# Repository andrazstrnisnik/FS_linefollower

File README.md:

# FS_linefollower
Line follower robot project

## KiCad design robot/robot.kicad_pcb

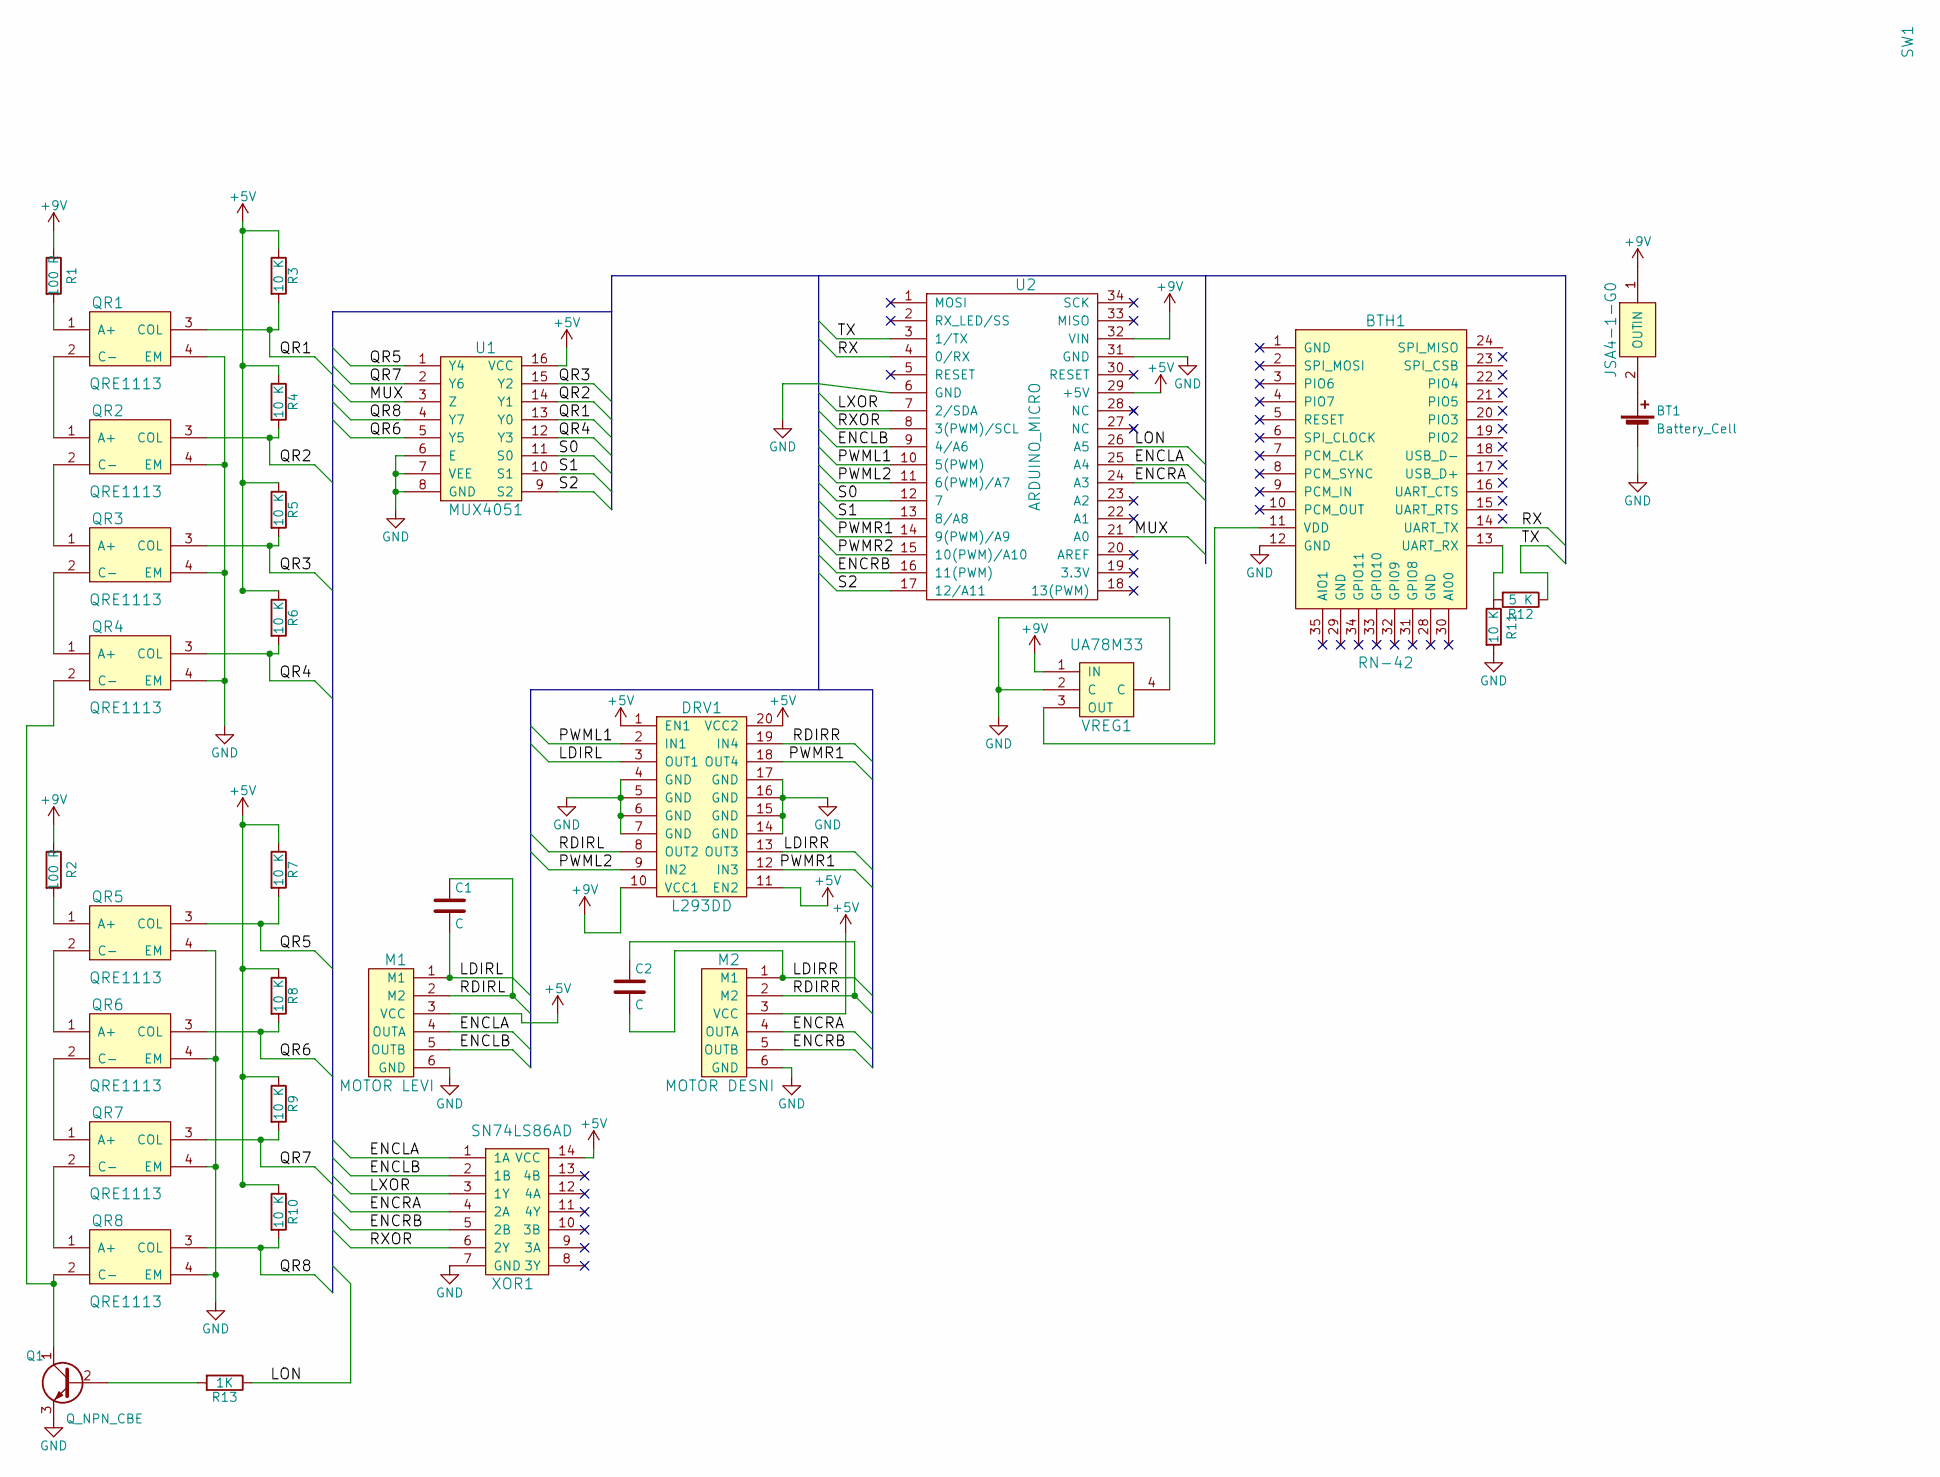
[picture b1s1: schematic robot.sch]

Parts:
BT1: Battery_Cell; battery_holder
BTH1: RN-42; MICROCHIP_RN-42-HID-RD1
C1, C2: C; C_0805_HandSoldering
DRV1: L293DD
M1: MOTOR LEVI; EM_Encoder
M2: MOTOR DESNI; EM_Encoder
Q1: Q_NPN_CBE; BSV52_NPN
QR1, QR2, QR3, QR4, QR5, QR6, QR7, QR8: QRE1113; QRE1113GR
R1, R2: 100 R; R_0805_HandSoldering
R3, R4, R5, R6, R7, R8, R9, R10, R11: 10 K; R_0805_HandSoldering
R12: 5 K; R_0805_HandSoldering
R13: 1K; R_0805_HandSoldering
SW1: JSA4-1-G0
U1: MUX4051; SOP63P600X175-16N
U2: ARDUINO_MICRO; ARDUINO_MICRO_SHIELD
VREG1: UA78M33; UA78M33-Q1_DCY_4
XOR1: SN74LS86AD; SOIC127P600X175-14N

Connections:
+5V: DRV1.1 (EN1), DRV1.11 (EN2), DRV1.20 (VCC2), M1.3 (VCC), M2.3 (VCC), R3.1, R4.1, R5.1, R6.1, R7.1, R8.1, R9.1, R10.1, U1.16 (VCC), U2.29 (+5V), XOR1.14 (VCC)
+9V: DRV1.10 (VCC1), R1.1, R2.1, SW1.1 (IN), U2.32 (VIN), VREG1.1 (IN)
/ENCLA: M1.4 (OUTA), U2.25 (A4), XOR1.1 (1A)
/ENCLB: M1.5 (OUTB), U2.9 (4/A6), XOR1.2 (1B)
/ENCRA: M2.4 (OUTA), U2.24 (A3), XOR1.4 (2A)
/ENCRB: M2.5 (OUTB), U2.16 (11(PWM)), XOR1.5 (2B)
/LDIRL: C1.2, DRV1.3 (OUT1), M1.1 (M1)
/LDIRR: C2.2, DRV1.13 (OUT3), M2.1 (M1)
/LON: R13.1, U2.26 (A5)
/LXOR: U2.7 (2/SDA), XOR1.3 (1Y)
/MUX: U1.3 (Z), U2.21 (A0)
/PWML1: DRV1.2 (IN1), U2.10 (5(PWM))
/PWML2: DRV1.9 (IN2), U2.11 (6(PWM)/A7)
/PWMR1: DRV1.12 (IN3), DRV1.18 (OUT4), U2.14 (9(PWM)/A9)
/PWMR2: U2.15 (10(PWM)/A10)
/QR1: QR1.3 (COL), R3.2, U1.13 (Y0)
/QR2: QR2.3 (COL), R4.2, U1.14 (Y1)
/QR3: QR3.3 (COL), R5.2, U1.15 (Y2)
/QR4: QR4.3 (COL), R6.2, U1.12 (Y3)
/QR5: QR5.3 (COL), R7.2, U1.1 (Y4)
/QR6: QR6.3 (COL), R8.2, U1.5 (Y5)
/QR7: QR7.3 (COL), R9.2, U1.2 (Y6)
/QR8: QR8.3 (COL), R10.2, U1.4 (Y7)
/RDIRL: C1.1, DRV1.8 (OUT2), M1.2 (M2)
/RDIRR: C2.1, DRV1.19 (IN4), M2.2 (M2)
/RX: BTH1.14 (UART_TX), U2.4 (0/RX)
/RXOR: U2.8 (3(PWM)/SCL), XOR1.6 (2Y)
/S0: U1.11 (S0), U2.12 (7)
/S1: U1.10 (S1), U2.13 (8/A8)
/S2: U1.9 (S2), U2.17 (12/A11)
/TX: R12.1, U2.3 (1/TX)
GND: BT1.2 (-), BTH1.12 (GND), DRV1.4 (GND), DRV1.5 (GND), DRV1.6 (GND), DRV1.7 (GND), DRV1.14 (GND), DRV1.15 (GND), DRV1.16 (GND), DRV1.17 (GND), M1.6 (GND), M2.6 (GND), Q1.3 (E), QR1.4 (EM), QR2.4 (EM), QR3.4 (EM), QR4.4 (EM), QR5.4 (EM), QR6.4 (EM), QR7.4 (EM), QR8.4 (EM), R11.2, U1.6 (E), U1.7 (VEE), U1.8 (GND), U2.6 (GND), U2.31 (GND), VREG1.2 (C), VREG1.4 (C), XOR1.7 (GND)
unnamed: BT1.1 (+), SW1.2 (OUT)
unnamed: BTH1.11 (VDD), VREG1.3 (OUT)
unnamed: BTH1.13 (UART_RX), R11.1, R12.2
unnamed: Q1.1 (C), QR4.2 (C-), QR8.2 (C-)
unnamed: Q1.2 (B), R13.2
unnamed: QR1.1 (A+), R1.2
unnamed: QR1.2 (C-), QR2.1 (A+)
unnamed: QR2.2 (C-), QR3.1 (A+)
unnamed: QR3.2 (C-), QR4.1 (A+)
unnamed: QR5.1 (A+), R2.2
unnamed: QR5.2 (C-), QR6.1 (A+)
unnamed: QR6.2 (C-), QR7.1 (A+)
unnamed: QR7.2 (C-), QR8.1 (A+)

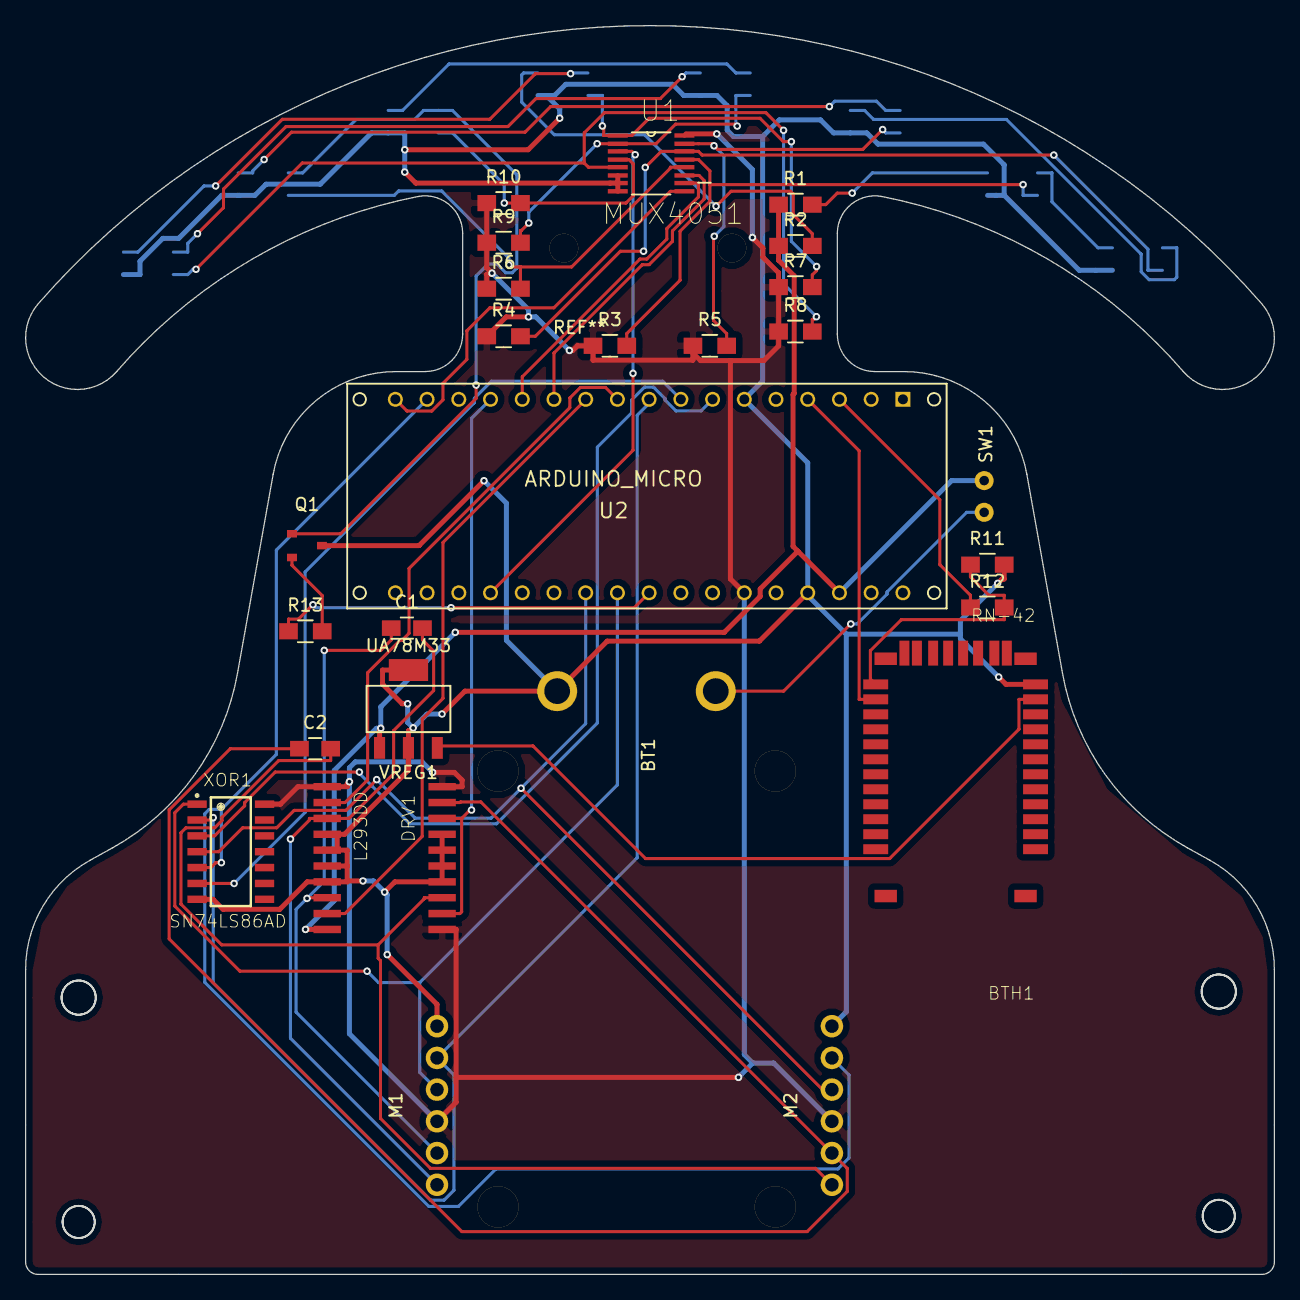
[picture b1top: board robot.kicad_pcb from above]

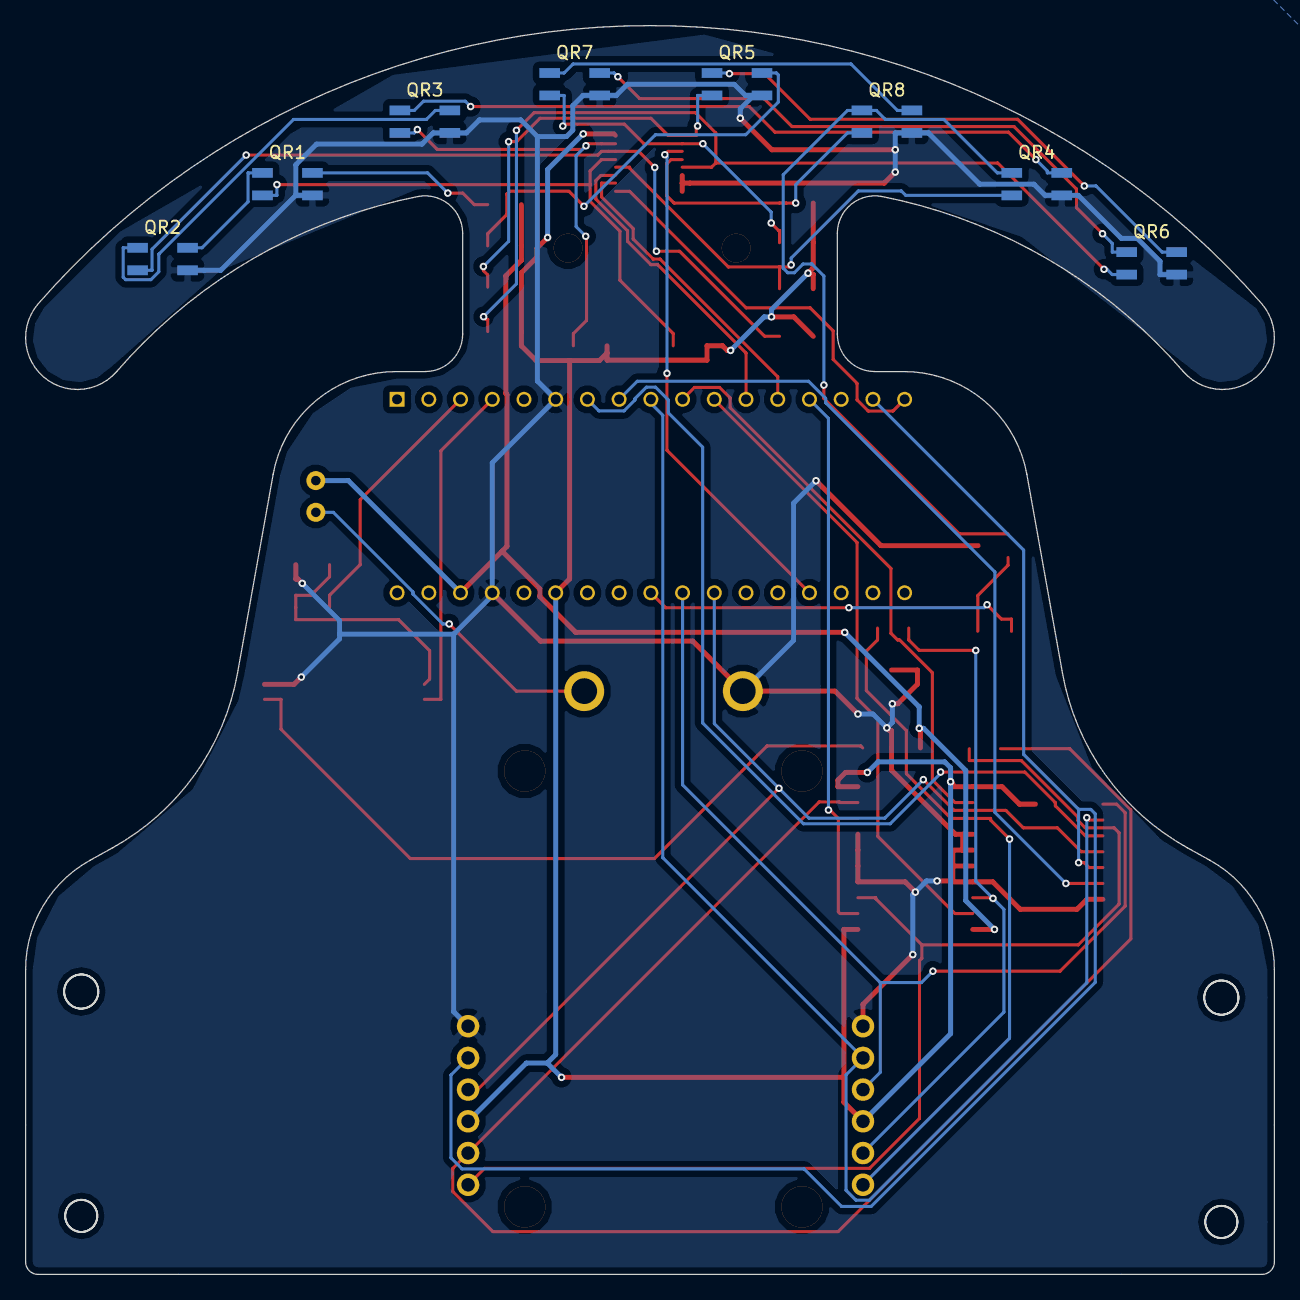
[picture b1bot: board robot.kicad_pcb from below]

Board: 2 copper layers, 100.0 x 99.9 mm, 34 parts (8 on the bottom side), 44 nets.

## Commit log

2017-02-27 KiCAD_starting
    Getting to know KiCAD software
2017-02-27 starting schematics
    Done few first steps
2017-03-06 upgrading scheme
2017-03-12 submiting sheme
2017-03-26 PCB design
    Adding pcb design with footprints with few 3D models.

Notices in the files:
parts and their libraries:
Copyright 2016 Accelerated Designs. All rights reserved.
